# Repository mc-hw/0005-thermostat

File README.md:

# Thermostat (0005)

A thermostat indicating _too low/OK/too high_ temperature with LEDS.

## Description

This circuit is a copy of [AVT-1742](./AVT1742.pdf) converted to Surface Mounted Technology.

## Assembly

This circuit should be assembled on a double-sided, SMT printed circuit board.

## Running

The device should be powered with 12VDC connected to J3 junction (mind the polarization).

Comparing to the original solution, either a thermistor embedded into the PCB or the external thermistor connected to
junction J1 can be used. Jumper JP1 should be soldered when the embedded thermistor is used, or de-soldered when the
external thermistor is used.

The high/lowh temperature thresholds should be calibrated using potentiometers P1 and P2, or external potentiometers
connected to J5 and J6. Jumper JP2 should be soldered when the embedded potentiometers are used, or de-soldered when the
external potentiometers are used.

The thresholds (low/ok/high) are presented with LED1 (high), LED2 (OK) and LED3 (low), or external LEDs connected to
junction J4 (LED current limiting resistors are required, open-collector outputs). Jumper JP3 should be soldered when
the embedded LEDs are used, or de-soldered when the embedded LEDs are not used.

The thresholds can be used to trigger external devices (e.g. using relays). External devices should be connected to
junction J2 (coil current limiting resistors are required, open-collector outputs; the current should be <80mA -
limitation of BC847B transistor; recommended current <40mA, as it's possible that two signals are enabled due to
incorrect calibration).

## Bill of materials

| Reference   | Qty | Value    | Footprint             |
|:------------|:----|:---------|:----------------------|
| C1,C2,C4,C5 | 4   | 100nF    | 0603                  |
| C3          | 1   | 470uF    | Electrolytic D=10mm   |
| D1,D2,D3    | 3   | 1N4148   | SOD-323               |
| J1          | 1   | EXT\_NTC | JST-SH 1x2 Vertical   |
| J2          | 1   | OUT      | JST-SH 1x4 Vertical   |
| J3          | 1   | PWR      | JST-SH 1x2 Vertical   |
| J4          | 1   | EXT\_LED | JST-SH 1x4 Vertical   |
| J5          | 1   | EXT\_P1  | JST-SH 1x3 Vertical   |
| J6          | 1   | EXT\_P2  | JST-SH 1x3 Vertical   |
| LED1        | 1   | RED      | 0603                  |
| LED2        | 1   | GREEN    | 0603                  |
| LED3        | 1   | BLUE     | 0603                  |
| NTC1        | 1   | 22k      | 0603                  |
| P1,P2       | 2   | 22k      | Bourns_3224W_Vertical |
| R1,R2,R3    | 3   | 10k      | 0603                  |
| R4,R5       | 2   | 1M       | 0603                  |
| R6,R7       | 2   | 2,2k     | 0603                  |
| R8,R9,R10   | 3   | 15k      | 0603                  |
| R11,R12,R13 | 3   | 1k       | 0603                  |
| T1,T2,T3    | 3   | BC847B   | SOT-23                |
| US1         | 1   | LM393    | TSSOP-8 4.4mm x 3mm   |
| US2         | 1   | 4011     | TSSOP-14 4.4mm x 5mm  |

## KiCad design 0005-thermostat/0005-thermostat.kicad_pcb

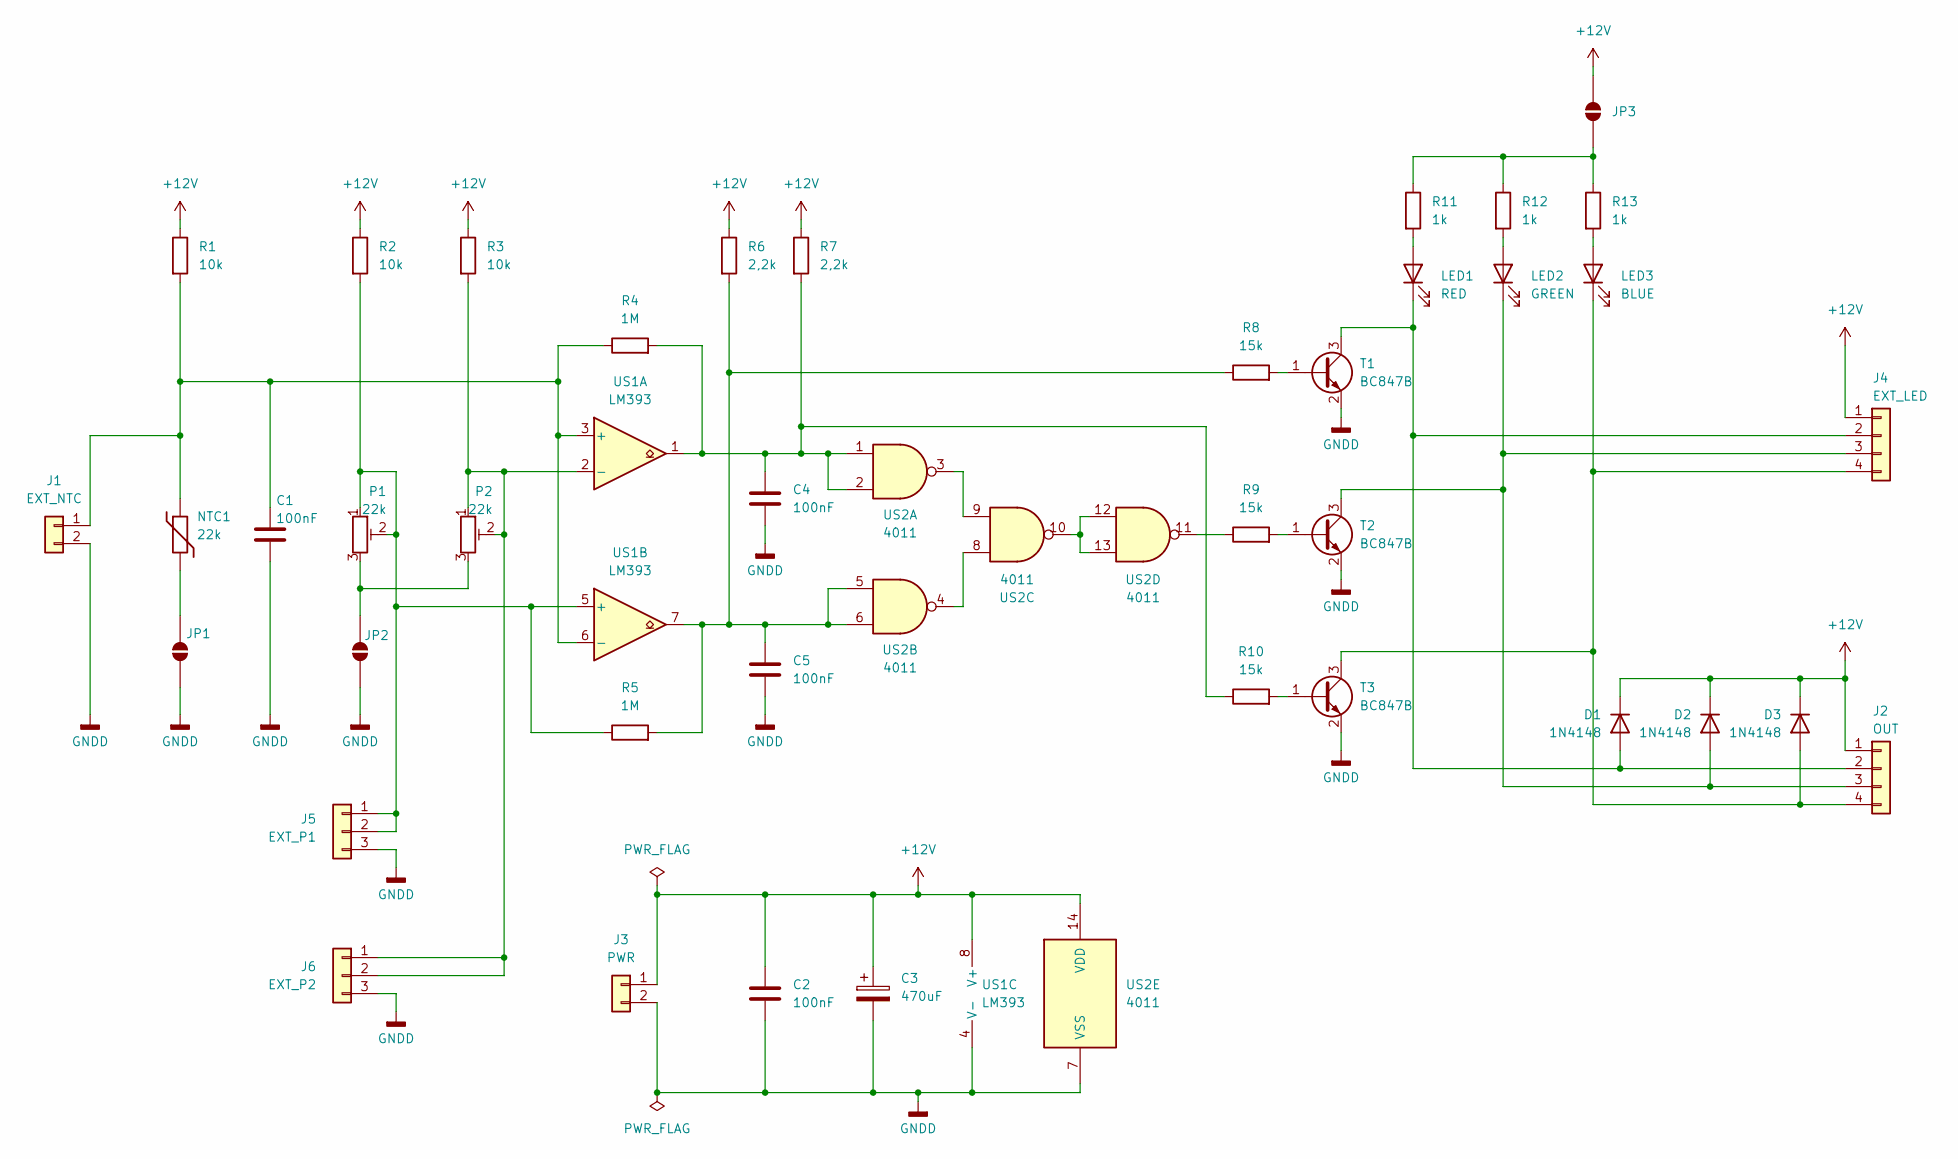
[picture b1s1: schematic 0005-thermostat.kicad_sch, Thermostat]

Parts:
C1, C2, C4, C5: 100nF; C_0603_1608Metric_Pad1.08x0.95mm_HandSolder
C3: 470uF; CP_Elec_10x10
D1, D2, D3: 1N4148; D_SOD-323_HandSoldering
J1: EXT_NTC; JST_SH_BM02B-SRSS-TB_1x02-1MP_P1.00mm_Vertical
J2: OUT; JST_SH_BM04B-SRSS-TB_1x04-1MP_P1.00mm_Vertical
J3: PWR; JST_SH_BM02B-SRSS-TB_1x02-1MP_P1.00mm_Vertical
J4: EXT_LED; JST_SH_BM04B-SRSS-TB_1x04-1MP_P1.00mm_Vertical
J5: EXT_P1; JST_SH_BM03B-SRSS-TB_1x03-1MP_P1.00mm_Vertical
J6: EXT_P2; JST_SH_BM03B-SRSS-TB_1x03-1MP_P1.00mm_Vertical
JP1, JP2, JP3: SolderJumper_2_Open; SolderJumper-2_P1.3mm_Open_Pad1.0x1.5mm
LED1: RED; LED_0603_1608Metric_Pad1.05x0.95mm_HandSolder
LED2: GREEN; LED_0603_1608Metric_Pad1.05x0.95mm_HandSolder
LED3: BLUE; LED_0603_1608Metric_Pad1.05x0.95mm_HandSolder
NTC1: 22k; R_0603_1608Metric_Pad0.98x0.95mm_HandSolder
P1, P2: 22k; Potentiometer_Bourns_3224W_Vertical
R1, R2, R3: 10k; R_0603_1608Metric_Pad0.98x0.95mm_HandSolder
R4, R5: 1M; R_0603_1608Metric_Pad0.98x0.95mm_HandSolder
R6, R7: 2,2k; R_0603_1608Metric_Pad0.98x0.95mm_HandSolder
R8, R9, R10: 15k; R_0603_1608Metric_Pad0.98x0.95mm_HandSolder
R11, R12, R13: 1k; R_0603_1608Metric_Pad0.98x0.95mm_HandSolder
T1, T2, T3: BC847B; SOT-23
US1: LM393; TSSOP-8_4.4x3mm_P0.65mm
US2: 4011; TSSOP-14_4.4x5mm_P0.65mm

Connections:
+12V: C2.1, C3.1, D1.1 (K), D2.1 (K), D3.1 (K), J2.1, J3.1, J4.1, JP3.1 (A), R1.1, R2.1, R3.1, R6.1, R7.1, US1.8 (V+), US2.14 (VDD)
GNDD: C1.2, C2.2, C3.2, C4.2, C5.2, J1.2, J1.MP, J2.MP, J3.2, J3.MP, J4.MP, J5.3, J5.MP, J6.3, J6.MP, JP1.1 (A), JP2.1 (A), T1.2 (E), T2.2 (E), T3.2 (E), US1.4 (V-), US2.7 (VSS)
unnamed: C4.1, R4.2, R7.2, R10.1, US1.1, US2.1, US2.2
unnamed: C5.1, R5.2, R6.2, R8.1, US1.7, US2.5, US2.6
unnamed: D1.2 (A), J2.2, J4.2, LED1.1 (K), T1.3 (C)
unnamed: D2.2 (A), J2.3, J4.3, LED2.1 (K), T2.3 (C)
unnamed: D3.2 (A), J2.4, J4.4, LED3.1 (K), T3.3 (C)
unnamed: C1.1, J1.1, NTC1.1, R1.2, R4.1, US1.3 (+), US1.6 (-)
unnamed: J5.1, J5.2, P1.1, P1.2, R2.2, R5.1, US1.5 (+)
unnamed: J6.1, J6.2, P2.1, P2.2, R3.2, US1.2 (-)
unnamed: JP1.2 (B), NTC1.2
unnamed: JP2.2 (B), P1.3, P2.3
unnamed: JP3.2 (B), R11.1, R12.1, R13.1
unnamed: LED1.2 (A), R11.2
unnamed: LED2.2 (A), R12.2
unnamed: LED3.2 (A), R13.2
unnamed: R9.1, US2.11
unnamed: R8.2, T1.1 (B)
unnamed: R9.2, T2.1 (B)
unnamed: R10.2, T3.1 (B)
unnamed: US2.3, US2.9
unnamed: US2.4, US2.8
unnamed: US2.10, US2.12, US2.13

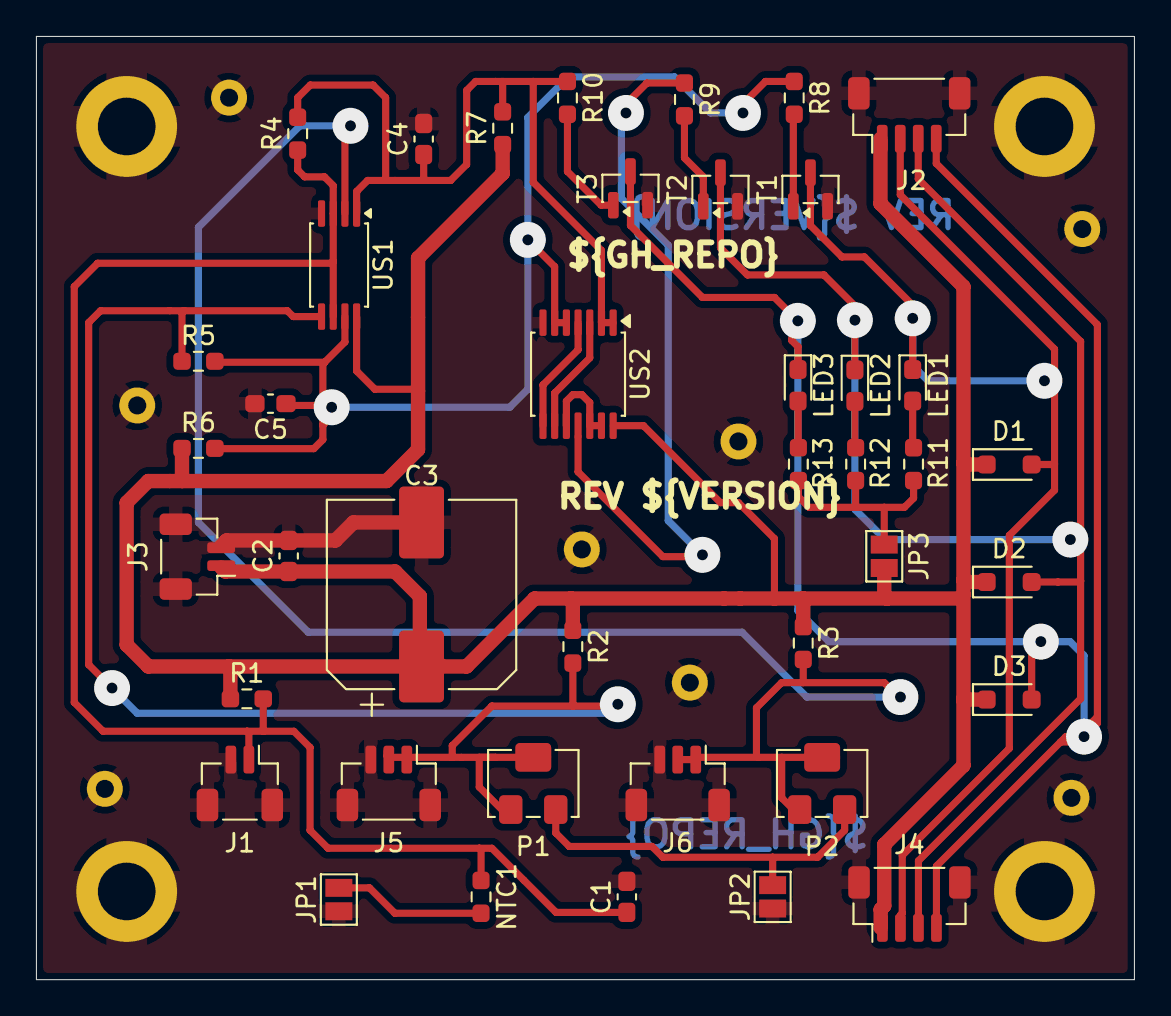
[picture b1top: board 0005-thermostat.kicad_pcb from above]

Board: 2 copper layers, 61.0 x 52.4 mm, 41 parts (0 on the bottom side), 23 nets.
